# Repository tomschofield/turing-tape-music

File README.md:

# turing-tape-music
A framework for a live music performance based on a turing machine whose rule set is defined by some material process. Project initiated by John Bowers with Tom Schofield

More details at http://digitalcultures.ncl.ac.uk/site/index.html#/grid/111 

Things others are likely to use are in the USEFUL_CLASSES folder!

Turing Tape Music

Copyright (c) 2016 Tom Schofield and John Bowers

Permission is hereby granted, free of charge, to any person obtaining a copy
of this software and associated documentation files (the "Software"), to deal
in the Software without restriction, including without limitation the rights
to use, copy, modify, merge, publish, distribute, sublicense, and/or sell
copies of the Software, and to permit persons to whom the Software is
furnished to do so, subject to the following conditions:

The above copyright notice and this permission notice shall be included in all
copies or substantial portions of the Software.

THE SOFTWARE IS PROVIDED "AS IS", WITHOUT WARRANTY OF ANY KIND, EXPRESS OR
IMPLIED, INCLUDING BUT NOT LIMITED TO THE WARRANTIES OF MERCHANTABILITY,
FITNESS FOR A PARTICULAR PURPOSE AND NONINFRINGEMENT. IN NO EVENT SHALL THE
AUTHORS OR COPYRIGHT HOLDERS BE LIABLE FOR ANY CLAIM, DAMAGES OR OTHER
LIABILITY, WHETHER IN AN ACTION OF CONTRACT, TORT OR OTHERWISE, ARISING FROM,
OUT OF OR IN CONNECTION WITH THE SOFTWARE OR THE USE OR OTHER DEALINGS IN THE
SOFTWARE.

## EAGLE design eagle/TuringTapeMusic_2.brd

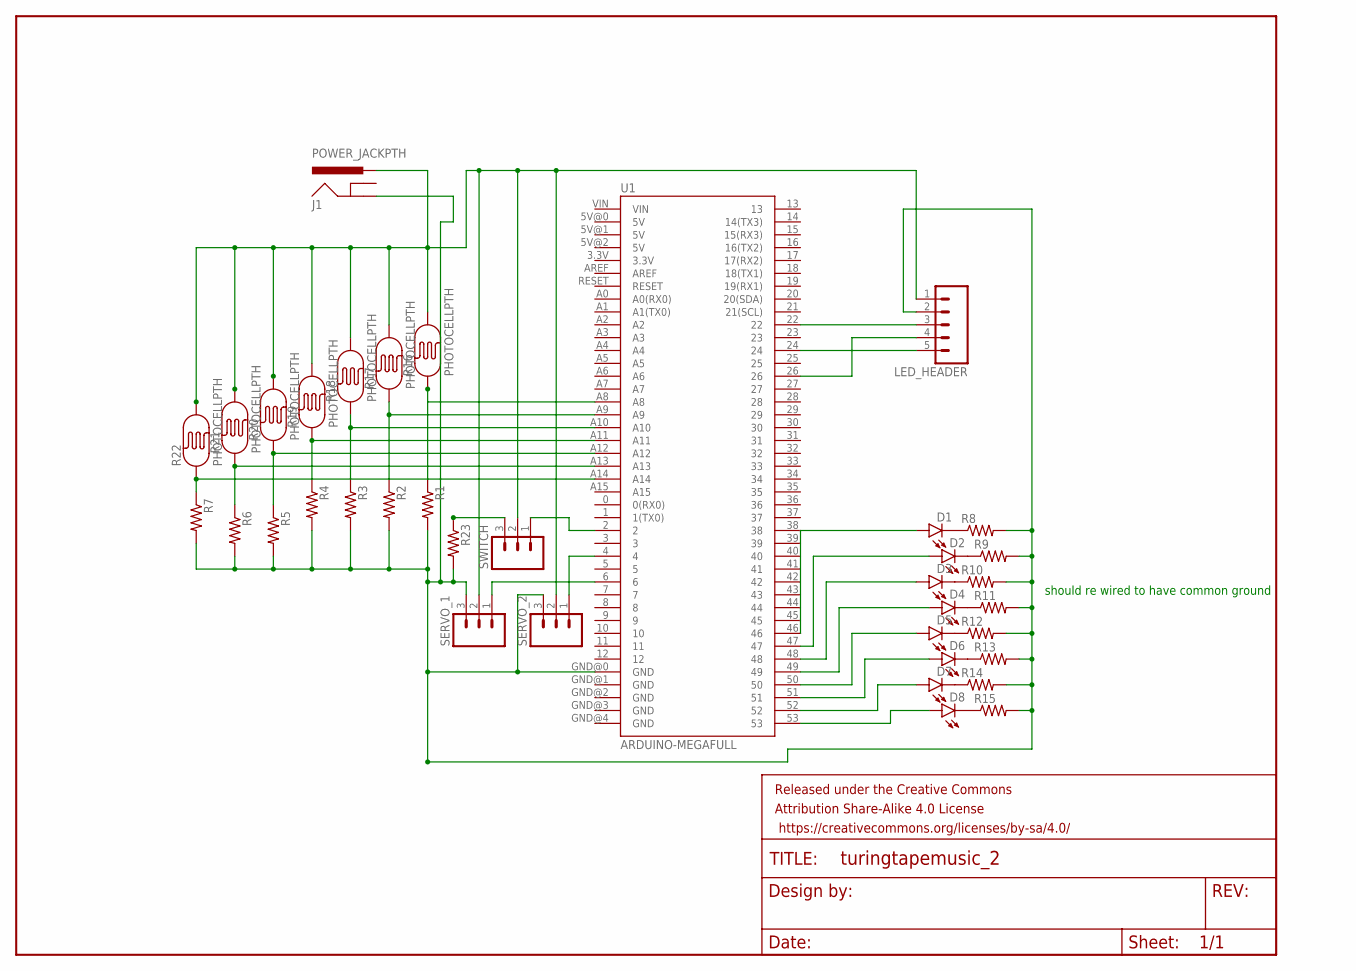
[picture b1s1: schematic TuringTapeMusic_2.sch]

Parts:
D1, D2, D3, D4, D5, D6, D7, D8: LED5MM
FRAME1: FRAME-LETTER; CREATIVE_COMMONS
J1: POWER_JACKPTH; POWER_JACK_PTH
LED_HEADER: M05LOCK; 1X05_LOCK
R1, R2, R3, R4, R5, R6, R7, R8, R9, R10, R11, R12, R13, R14, R15, R23: RESISTORPTH-1/4W; AXIAL-0.4
R16, R17, R18, R19, R20, R21, R22: PHOTOCELLPTH; PHOTOCELL
SERVO_1, SERVO_2: M03LOCK; 1X03_LOCK
SWITCH: M03LOCK; 1X03_LOCK
U1: ARDUINO-MEGAFULL; ARDUINO_MEGA

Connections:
unnamed: R1.P$1 (1), R16.1, U1.A8
unnamed: R2.P$1 (1), R17.1, U1.A9
unnamed: R5.P$1 (1), R20.1, U1.A12
unnamed: R3.P$1 (1), R18.1, U1.A10
unnamed: R6.P$1 (1), R21.1, U1.A13
unnamed: R4.P$1 (1), R19.1, U1.A11
unnamed: R7.P$1 (1), R22.1, U1.A14
unnamed: D1.K (C), R8.P$1 (1)
unnamed: D2.K (C), R9.P$1 (1)
unnamed: D3.K (C), R10.P$1 (1)
unnamed: D4.K (C), R11.P$1 (1)
unnamed: D5.K (C), R12.P$1 (1)
unnamed: D6.K (C), R13.P$1 (1)
unnamed: D7.K (C), R14.P$1 (1)
unnamed: D8.K (C), R15.P$1 (1)
unnamed: D1.A, U1.46
unnamed: D2.A, U1.47
unnamed: D3.A, U1.48
unnamed: D4.A, U1.49
unnamed: D5.A, U1.50
unnamed: D6.A, U1.51
unnamed: D7.A, U1.52
unnamed: D8.A, U1.53
unnamed: LED_HEADER.5, U1.24
unnamed: LED_HEADER.4, U1.26
unnamed: LED_HEADER.3, U1.22
unnamed: SERVO_2.1, U1.4
unnamed: SERVO_1.1, U1.6
unnamed: SWITCH.1, U1.2
unnamed: R23.P$1 (1), SWITCH.3
unnamed: J1.GND, LED_HEADER.2, R1.P$2 (2), R2.P$2 (2), R3.P$2 (2), R4.P$2 (2), R5.P$2 (2), R6.P$2 (2), R7.P$2 (2), R8.P$2 (2), R9.P$2 (2), R10.P$2 (2), R11.P$2 (2), R12.P$2 (2), R13.P$2 (2), R14.P$2 (2), R15.P$2 (2), R23.P$2 (2), SERVO_1.3, SERVO_2.3, U1.GND@0 (GND)
unnamed: J1.PWR, LED_HEADER.1, R16.2, R17.2, R18.2, R19.2, R20.2, R21.2, R22.2, SERVO_1.2, SERVO_2.2, SWITCH.2

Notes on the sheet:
should re wired to have common ground

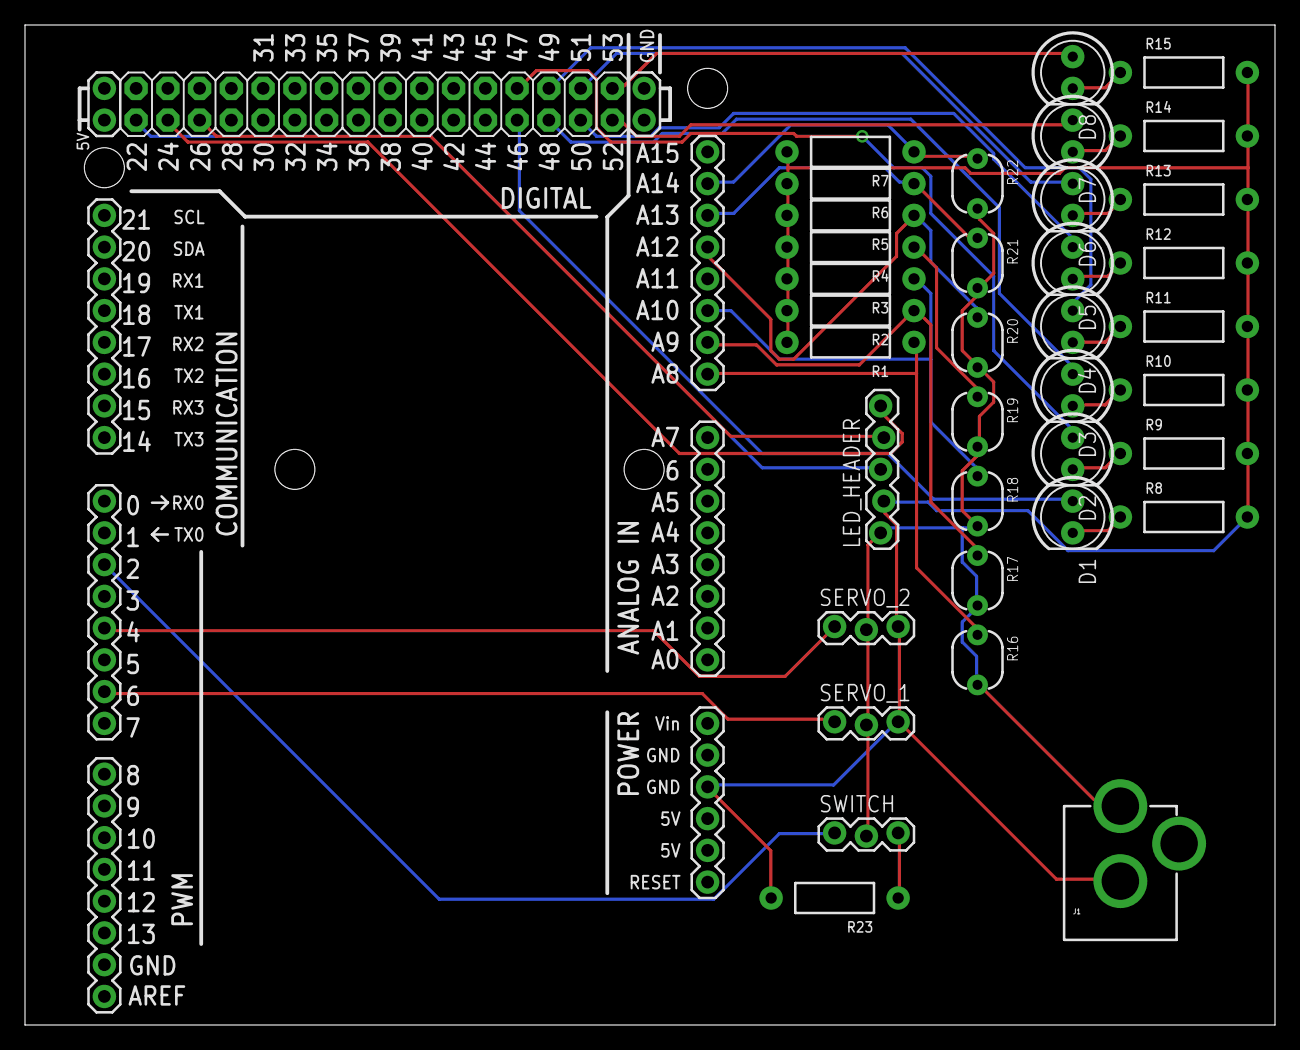
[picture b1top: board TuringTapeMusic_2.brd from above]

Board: 2 copper layers, 100.0 x 80.0 mm, 38 parts (0 on the bottom side), 32 nets.

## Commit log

2016-10-28 major commit pre piksel now includes eagle files and schematic arduino sketch contains no delays becuase of added Timer class
2016-10-28 added license and useful things folder
2016-10-28 corrected typo in license

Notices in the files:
parts and their libraries:
SparkFun-Aesthetics: Licensing: Creative Commons ShareAlike 4.0 International - https://creativecommons.org/licenses/by-sa/4.0
SparkFun-Aesthetics: Released under the Creative Commons Attribution Share-Alike 4.0 License
SparkFun-Aesthetics: https://creativecommons.org/licenses/by-sa/4.0
